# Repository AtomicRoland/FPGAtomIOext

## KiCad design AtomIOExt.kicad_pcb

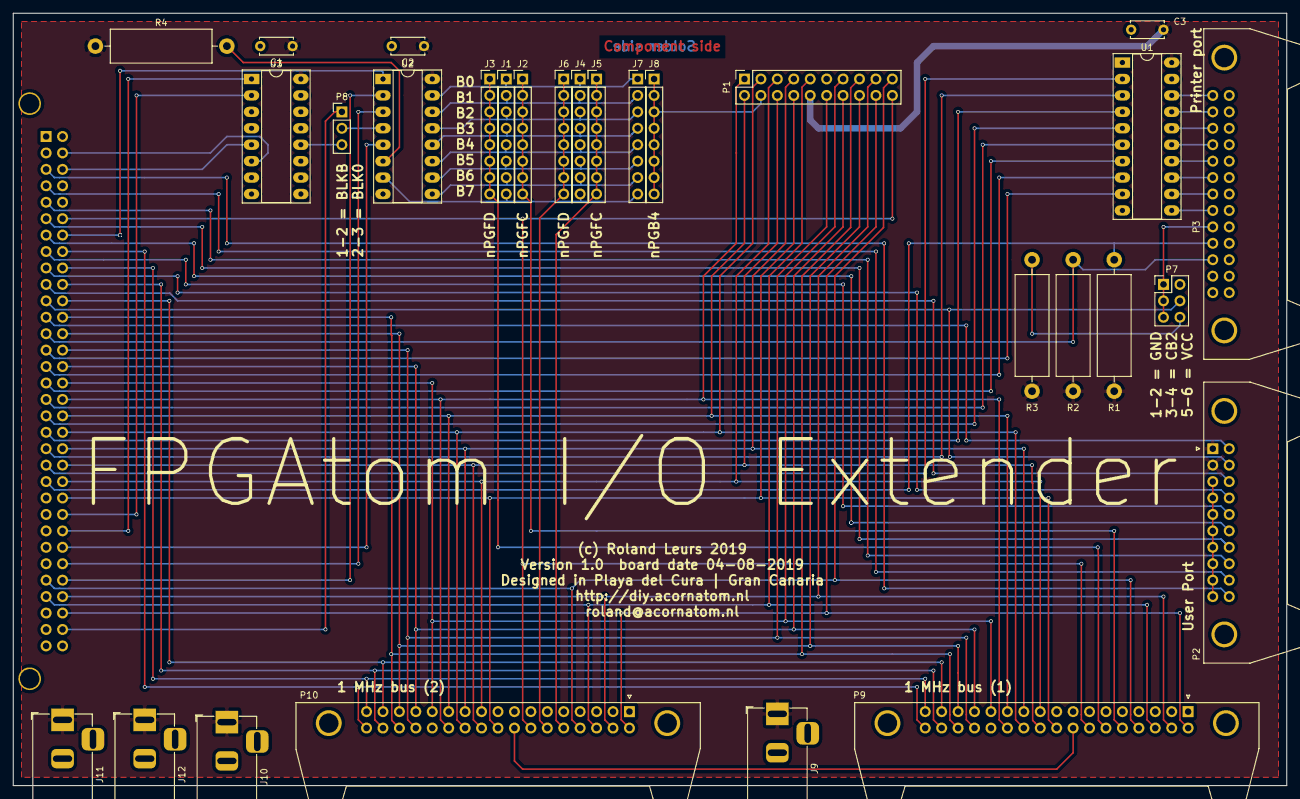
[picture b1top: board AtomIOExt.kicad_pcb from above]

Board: 2 copper layers, 196.9 x 119.4 mm, 30 parts (1 on the bottom side), 79 nets.

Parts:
C1, C2, C3: 100nF; C_Disc_D5.0mm_W2.5mm_P5.00mm
J1: I/O sel BUS1; PinHeader_1x08_P2.54mm_Vertical
J2, J3, J5, J6, J8: Conn_01x08; PinHeader_1x08_P2.54mm_Vertical
J4: I/O sel BUS2; PinHeader_1x08_P2.54mm_Vertical
J7: I/O sel PL8; PinHeader_1x08_P2.54mm_Vertical
J9: Jack-DC x 4; BarrelJack_Horizontal
J10, J11, J12: Jack-DC; BarrelJack_Horizontal
P1: ATOM PL8; PinSocket_2x10_P2.54mm_Vertical
P2: USER PORT; IDC-Header_2x10_P2.54mm_Horizontal_Lock
P3: PRINTER; IDC-Header_2x13_P2.54mm_Horizontal_Lock
P6: CONN_02X32; DIN41612_B_2x32_Horizontal
P7: 8th printer bit; PinHeader_2x03_P2.54mm_Vertical
P8: I/O preselect; PinHeader_1x03_P2.54mm_Vertical
P9, P10: 1MHZ BUS; IDC-Header_2x17_P2.54mm_Horizontal_Lock
R1, R2, R3, R4: 4k7; R_Axial_DIN0516_L15.5mm_D5.0mm_P20.32mm_Horizontal
U1: 74LS541; DIP-20_W7.62mm_Socket_LongPads
U2, U3: 74LS138; DIP-16_W7.62mm_Socket_LongPads

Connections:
+5V: C1.1, C2.1, C3.1, J9.1, J10.1, J11.1, J12.1, P1.10, P2.1, P2.3, R1.2, R2.2, R3.1, R4.1, U1.20, U2.16, U3.16
/A0: P1.14, P6.b15, P9.27, P10.27
/A1: P1.12, P6.b14, P9.28, P10.28
/A2: P1.16, P6.b13, P9.29, P10.29
/A3: P1.15, P6.b12, P9.30, P10.30
/A4: P6.b11, P9.31, P10.31
/A5: P6.b10, P9.32, P10.32
/A6: P6.b9, P9.33, P10.33
/A7: P6.b8, P9.34, P10.34
/A8: P6.b7, U2.1
/A9: P6.b28, U2.2
/A10: P6.b27, U2.3
/A11: P6.b26, U2.5
/A12: P6.b25, U3.1
/A13: P6.b24, U3.2
/A14: P6.b3, U3.5
/A15: P6.b2, U3.6
/ANALOG_IN: P9.16, P10.16
/BLK0: P6.b31, P8.1
/CA1: P3.19, P6.a22, R1.1
/CA2: P6.a21, U1.2
/CB1: P2.2, P6.a12
/CB2: P2.4, P6.a11, P7.4
/D0: P1.8, P6.b23, P9.18, P10.18
/D1: P1.5, P6.b22, P9.19, P10.19
/D2: P1.6, P6.b21, P9.20, P10.20
/D3: P1.7, P6.b20, P9.21, P10.21
/D4: P1.3, P6.b19, P9.22, P10.22
/D5: P1.2, P6.b18, P9.23, P10.23
/D6: P1.1, P6.b17, P9.24, P10.24
/D7: P1.13, P6.b16, P9.25, P10.25
/IRQ: P1.19, P6.a28, P9.8, P10.8
/NMI: P1.9, P6.a29, P9.6, P10.6
/NPGB4: J8.1, J8.2, J8.3, J8.4, J8.5, J8.6, J8.7, J8.8, P1.4
/NPGFC_1: J2.1, J2.2, J2.3, J2.4, J2.5, J2.6, J2.7, J2.8, P9.10
/NPGFC_2: J5.1, J5.2, J5.3, J5.4, J5.5, J5.6, J5.7, J5.8, P10.10
/NPGFD_1: J3.1, J3.2, J3.3, J3.4, J3.5, J3.6, J3.7, J3.8, P9.12
/NPGFD_2: J6.1, J6.2, J6.3, J6.4, J6.5, J6.6, J6.7, J6.8, P10.12
/PA0: P6.a20, U1.3
/PA1: P6.a19, U1.4
/PA2: P6.a18, U1.5
/PA3: P6.a17, U1.6
/PA4: P6.a16, U1.7
/PA5: P6.a15, U1.8
/PA6: P6.a14, U1.9
/PA7: P3.21, P6.a13, R2.1
/PB0: P2.6, P6.a10
/PB1: P2.8, P6.a9
/PB2: P2.10, P6.a8
/PB3: P2.12, P6.a7
/PB4: P2.14, P6.a6
/PB5: P2.16, P6.a5
/PB6: P2.18, P6.a4
/PB7: P2.20, P6.a3
/PHI2: P1.17, P6.b29, P9.4, P10.4
/RESET: P1.20, P6.b6, P9.14, P10.14
/RW: P1.18, P6.b30, P9.2, P10.2
/nB0: J1.1, J4.1, J7.1, U2.15
/nB1: J1.2, J4.2, J7.2, U2.14
/nB2: J1.3, J4.3, J7.3, U2.13
/nB3: J1.4, J4.4, J7.4, U2.12
/nB4: J1.5, J4.5, J7.5, U2.11
/nB5: J1.6, J4.6, J7.6, U2.10
/nB6: J1.7, J4.7, J7.7, U2.9
/nB7: J1.8, J4.8, J7.8, U2.7
GND: C1.2, C2.2, C3.2, J9.2, J10.2, J11.2, J12.2, P1.11, P2.5, P2.7, P2.9, P2.11, P2.13, P2.15, P2.17, P2.19, P3.2, P3.4, P3.6, P3.8, P3.10, P3.12, P3.14, P3.16, P3.18, P3.20, P3.22, P3.24, P6.a32, P6.b32, P7.2, P9.1, P9.3, P9.5, P9.7, P9.9, P9.11, P9.13, P9.15, P9.17, P9.26, P10.1, P10.3, P10.5, P10.7, P10.9, P10.11, P10.13, P10.15, P10.17, P10.26, U1.1, U1.10, U1.19, U2.8, U3.3, U3.4, U3.8
unnamed: P3.1, U1.18
unnamed: P3.3, U1.17
unnamed: P3.5, U1.16
unnamed: P3.7, U1.15
unnamed: P3.9, U1.14
unnamed: P3.11, U1.13
unnamed: P3.13, U1.12
unnamed: P3.15, U1.11
unnamed: P3.17, P7.1, P7.3, P7.5
unnamed: P7.6, R3.2
unnamed: P8.2, U2.4
unnamed: P8.3, U3.12
unnamed: R4.2, U2.6
